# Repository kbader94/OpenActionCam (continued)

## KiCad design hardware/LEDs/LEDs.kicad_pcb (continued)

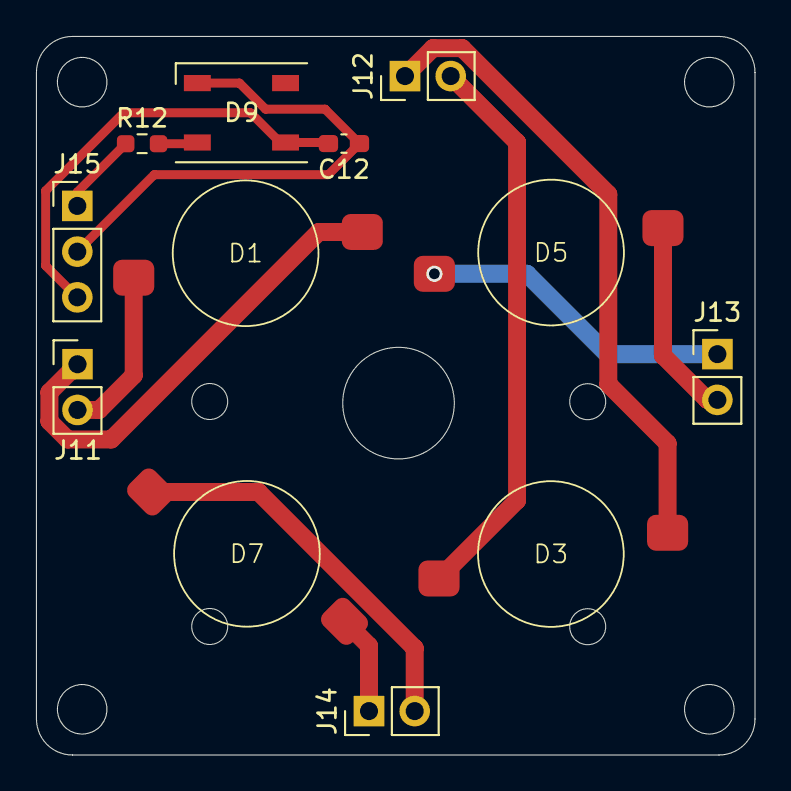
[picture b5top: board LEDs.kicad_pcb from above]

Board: 2 copper layers, 39.9 x 39.9 mm, 12 parts (0 on the bottom side), 11 nets.

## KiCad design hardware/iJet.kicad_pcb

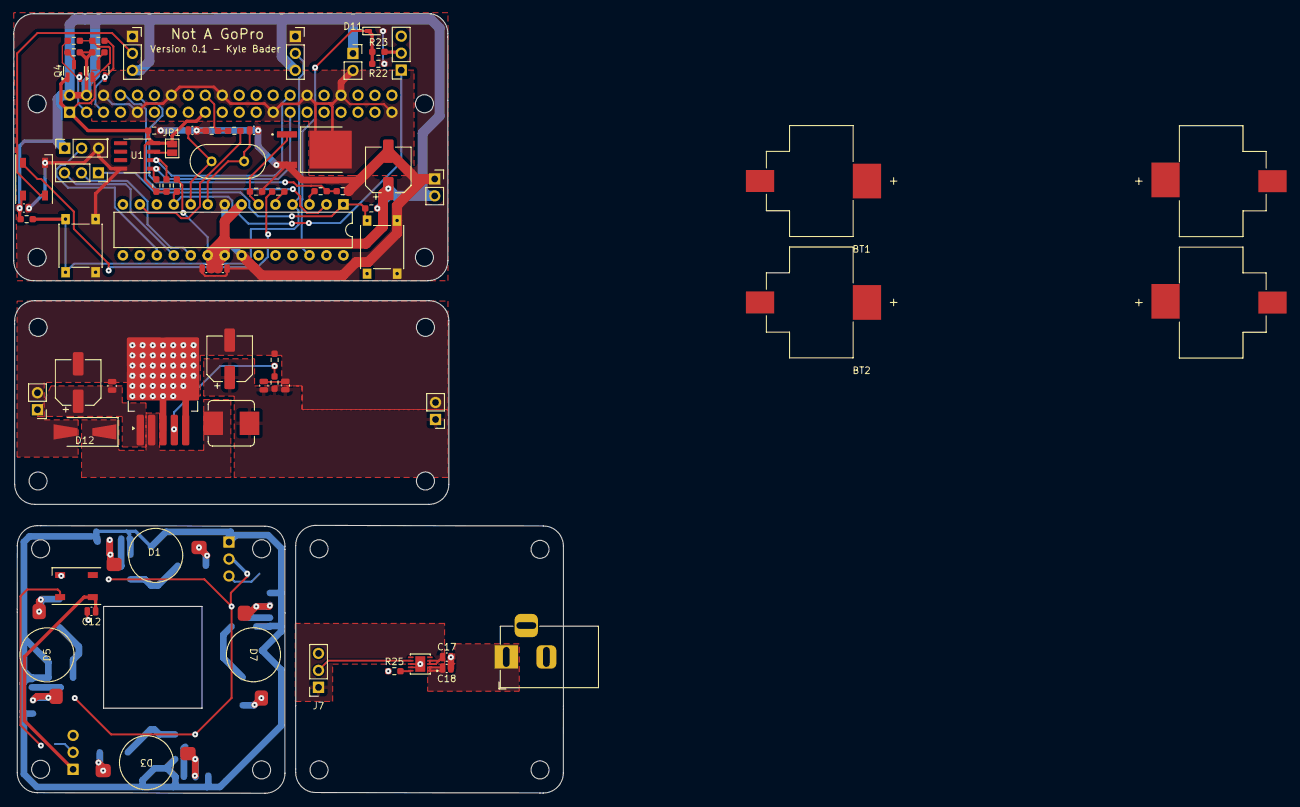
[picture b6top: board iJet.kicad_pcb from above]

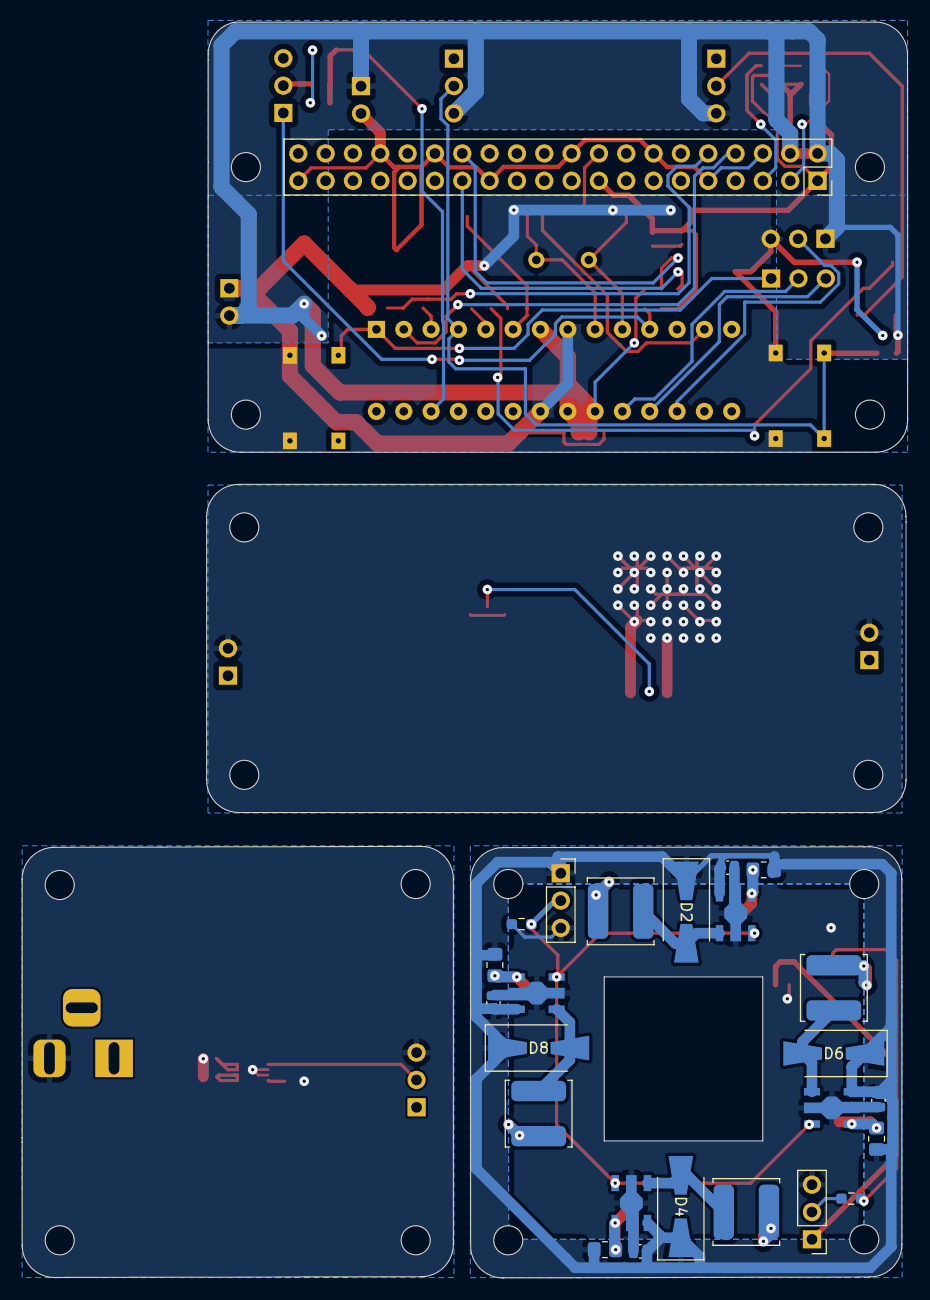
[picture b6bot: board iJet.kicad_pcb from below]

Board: 2 copper layers, 82.3 x 116.7 mm, 109 parts (25 on the bottom side), 48 nets.

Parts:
BT1, BT2: Battery_Cell; BAT_254
C1: 100n; R_0603_1608Metric_Pad0.98x0.95mm_HandSolder
C2: 100 UF; C_0504_1310Metric_Pad0.83x1.28mm_HandSolder
C3, C4, C5: 100 uF; C_0504_1310Metric_Pad0.83x1.28mm_HandSolder
C6, C12, C19: 0.1uF; C_0504_1310Metric_Pad0.83x1.28mm_HandSolder
C7: C_Polarized; CP_Elec_6.3x5.9
C8: 100uF 25V; CP_Elec_6.3x5.9
C9: 330uF 10V; CP_Elec_6.3x5.9
C10: 10nF; C_0504_1310Metric_Pad0.83x1.28mm_HandSolder
C11: 0.1uF 25V; C_0504_1310Metric_Pad0.83x1.28mm_HandSolder
C13, C14: 100nF; C_0504_1310Metric_Pad0.83x1.28mm_HandSolder
C15, C16: 22 pF; C_0504_1310Metric_Pad0.83x1.28mm_HandSolder
C17, C18: 10uF XR5/7; C_0504_1310Metric_Pad0.83x1.28mm_HandSolder
D1, D3: 3W LED; BEAD-3W-W-120-04
D2, D4, D6, D8: SS14; D_SMA-SMB_Universal_Handsoldering
D5, D7: LED; BEAD-3W-W-120-04
D9, D10: WS2812B; LED_WS2812B_PLCC4_5.0x5.0mm_P3.2mm
D11: 5.1V Zener; D_SC-80_HandSoldering
D12: 1N5825; D_SMA-SMB_Universal_Handsoldering
J1: GPIO; PinSocket_2x20_P2.54mm_Vertical
J2: Status_LED_Header; PinHeader_1x03_P2.54mm_Vertical
J3: HP_LED_Header; PinSocket_1x03_P2.54mm_Vertical
J4: Barrel_Jack; BarrelJack_Horizontal
J5: Battery_In; PinHeader_1x02_P2.54mm_Vertical
J6: 5V Out; PinHeader_1x02_P2.54mm_Vertical
J7: Conn_01x03_Socket; PinSocket_1x03_P2.54mm_Vertical
J12: Battery_Meas; PinSocket_1x03_P2.54mm_Vertical
J13: ICSP_Header_2; PinSocket_1x03_P2.54mm_Vertical
J14: 5V_In; PinSocket_1x02_P2.54mm_Vertical
J15: Stat_LED; PinSocket_1x03_P2.54mm_Vertical
J16: ICSP_Header_1; PinSocket_1x03_P2.54mm_Vertical
J17: Button_Header; PinSocket_1x03_P2.54mm_Vertical
J18: RPI_POWER; PinSocket_1x02_P2.54mm_Vertical
JP1: ID_WP; SolderJumper-2_P1.3mm_Open_Pad1.0x1.5mm
L1, L2, L3, L4: 68 uH; L_TDK_VLS6045EX_VLS6045AF
L5: 33uH; L_Bourns_SRP7028A_7.3x6.6mm
MH1, MH1#2, MH1#3, MH2, MH2#2, MH2#3, MH3, MH3#2, MH3#3, MH4, MH4#2, MH4#3, MH4#4, MH4#5, MH4#6, MH4#7: MountingHole_2.7mm_M2.5
Q2: AOD4184A; DPAK228P994X240-4N
Q3, Q4: BSS138; SOT-23
R1, R2: 3.9k; R_0603_1608Metric_Pad0.98x0.95mm_HandSolder
R3: 0.15 Ohm; R_0805_2012Metric_Pad1.20x1.40mm_HandSolder
R4, R5, R6: 0.15; R_0805_2012Metric_Pad1.20x1.40mm_HandSolder
R7, R11, R13, R14, R15, R16, R21, R23, R24: 10K; R_0603_1608Metric_Pad0.98x0.95mm_HandSolder
R8: 220 Ohm (Opt); R_0603_1608Metric_Pad0.98x0.95mm_HandSolder
R9: 3.065 K; R_0603_1608Metric_Pad0.98x0.95mm_HandSolder
R10, R25: 1K; R_0603_1608Metric_Pad0.98x0.95mm_HandSolder
R12, R26: R; R_0603_1608Metric_Pad0.98x0.95mm_HandSolder
R17, R20: 3.3K; R_0603_1608Metric_Pad0.98x0.95mm_HandSolder
R18, R19: 2K; R_0603_1608Metric_Pad0.98x0.95mm_HandSolder
R22: 15K; R_0603_1608Metric_Pad0.98x0.95mm_HandSolder
SW1: SW_DIP_x01; Button_Sw_THT
SW2: SW_Reset; Button_Sw_THT
U1: CAT24C256; SOIC127P600X175-8N
U2: LM2596S-ADJ; TO-263-5_TabPin3
U4: ATmega328-P; DIP-28_W7.62mm
U5, U6, U7, U8: PT4115; SOT-89-5
U9: MCP73213-A6SI_MF; SON50P300X300X100-11N
Y2: 16 Mhz; Crystal_HC49-U_Vertical

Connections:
+3V3: C1.1, J1.1, J1.17, JP1.2 (B), Q3.1 (G), Q4.1 (G), R1.1, R2.1, R13.2, R16.2, U1.8 (VCC)
+5V: C6.2, C7.1, C9.1, C10.2, C12.2, C13.2, C14.2, C19.1, D9.1 (VDD), D10.1 (VDD), J1.2, J1.4, J2.1, J6.1, J14.2, J15.3, J16.1, J17.3, J18.1, L5.2, R9.1, R14.2, R15.2, R21.1, R24.1, R26.1, U4.7 (VCC), U4.20 (AVCC), U4.21 (AREF)
+BATT: C2.1, C3.1, C4.1, C5.1, C8.1, C11.1, C17.1, D2.1 (K), D4.1 (K), D6.1 (K), D8.1 (K), J3.1, J5.1, J7.1, R3.1, R4.1, R5.1, R6.1, U2.1 (VIN), U5.5 (VIN), U6.5 (VIN), U7.5 (VIN), U8.5 (VIN), U9.3 (VBAT), U9.4 (VBAT)
/GPIO2/SDA1: J1.3, Q4.2 (S), R16.1
/GPIO3/SCL1: J1.5, Q3.2 (S), R13.1
/GPIO14/TXD0: J1.8, U4.2 (PD0)
/GPIO15/RXD0: J1.10, R17.2, R18.1
/GPIO24: J1.18, R19.1, R20.2
/ID_SCL: J1.28, R2.2, U1.6 (SCL)
/ID_SDA: J1.27, R1.2, U1.5 (SDA)
/LED Array/LED_En: J3.2, R11.1, U5.3 (DIM), U6.3 (DIM), U7.3 (DIM), U8.3 (DIM)
/LED Array/Status_DIN: J2.2, R8.1, R12.1, U4.5 (PD3)
/Pi_Int: R20.1, U4.13 (PD7)
/Pi_Rx: R17.1, U4.3 (PD1)
/Power Port and Charger/12V_IN: C18.1, J4.1, U9.1 (VDD), U9.2 (VDD)
/Power Port and Charger/Chrg_Stat: J7.2, J12.1, R26.2, U4.11 (PD5), U9.7 (STAT)
/Power State/BDI: J17.2, R24.2, SW1.1, U4.4 (PD2)
/Power State/Batt_Lvl: D11.1 (K), J12.2, R22.2, R23.1, R23.2, U4.26 (PC3)
/Power State/MISO: J13.3, U4.18 (PB4)
/Power State/MOSI: J16.2, U4.17 (PB3)
/Power State/Pi_En: Q2.1, R7.1, U4.6 (PD4)
/Power State/Reset: J13.1, R21.2, SW2.1, U4.1 (~RESET/PC6)
/Power State/SCK: J13.2, U4.19 (PB5)
/Power Supply/V_Out_Dirty: D12.1 (K), L5.1, U2.2 (OUT)
/SCL: Q3.3 (D), R14.1
/SDA: Q4.3 (D), R15.1
GND: C1.2, C2.2, C3.2, C4.2, C5.2, C6.1, C7.2, C8.2, C9.2, C10.1, C11.2, C12.1, C13.1, C14.1, C15.2, C16.2, C17.2, C18.2, C19.2, D9.3 (VSS), D10.3 (VSS), D11.2 (A), D12.2 (A), J2.3, J3.3, J4.2, J5.2, J6.2, J7.3, J14.1, J15.1, J16.3, J17.1, Q2.3, R7.2, R10.1, R11.2, R18.2, R19.2, R22.1, R25.1, SW1.2, SW2.2, U1.4 (GND), U2.3 (GND), U2.5 (~ON/OFF), U4.8 (GND), U4.22 (GND), U5.2 (GND), U6.2 (GND), U7.2 (GND), U8.2 (GND), U9.8 (VSS), U9.9 (VSS), U9.11 (EP)
unnamed: D1.2 (A), R3.2, U5.4 (CSN)
unnamed: D1.1 (K), L1.1
unnamed: D2.2 (A), L1.2, U5.1 (SW)
unnamed: D3.2 (A), R4.2, U6.4 (CSN)
unnamed: D3.1 (K), L2.1
unnamed: D4.2 (A), L2.2, U6.1 (SW)
unnamed: D5.2 (A), R5.2, U7.4 (CSN)
unnamed: D5.1 (K), L3.1
unnamed: D6.2 (A), L3.2, U7.1 (SW)
unnamed: D7.2 (A), R6.2, U8.4 (CSN)
unnamed: D7.1 (K), L4.1
unnamed: D8.2 (A), L4.2, U8.1 (SW)
unnamed: D9.4 (DIN), R12.2
unnamed: D10.4 (DIN), R8.2
unnamed: D10.2 (DOUT), J15.2
unnamed: JP1.1 (A), U1.7 (WP)
unnamed: R9.2, R10.2, U2.4 (FB)
unnamed: C15.1, U4.9 (XTAL1/PB6), Y2.2
unnamed: C16.1, U4.10 (XTAL2/PB7), Y2.1
unnamed: R25.2, U9.10 (PROG)
Pi_Gnd: J1.6, J1.9, J1.14, J1.20, J1.25, J1.30, J1.34, J1.39, J18.2, Q2.4

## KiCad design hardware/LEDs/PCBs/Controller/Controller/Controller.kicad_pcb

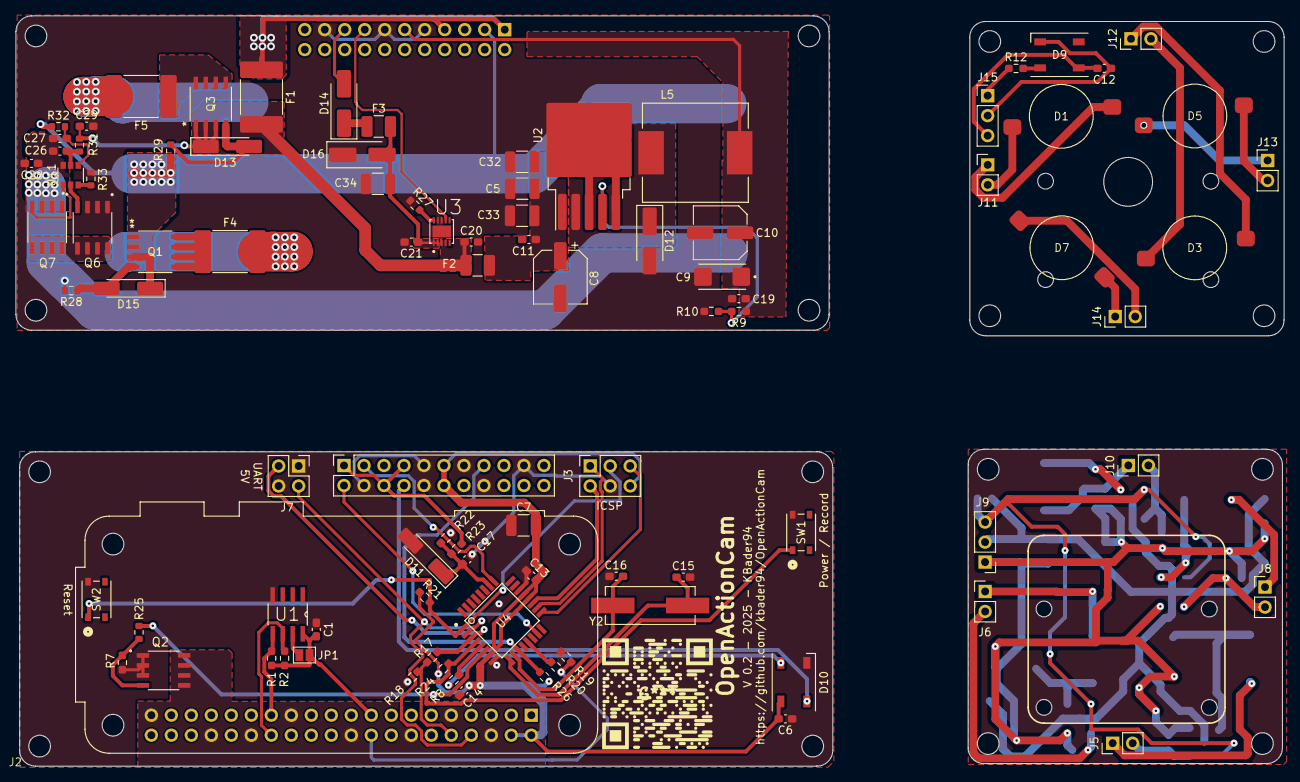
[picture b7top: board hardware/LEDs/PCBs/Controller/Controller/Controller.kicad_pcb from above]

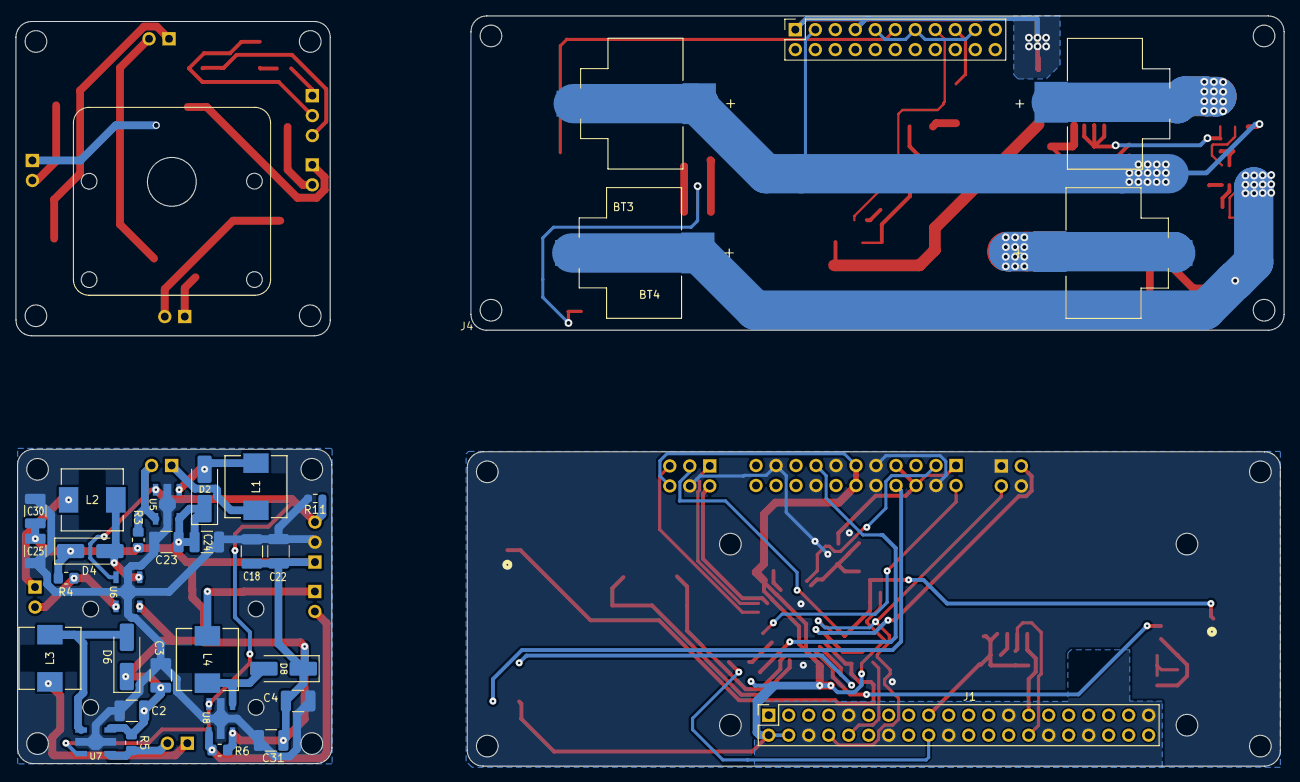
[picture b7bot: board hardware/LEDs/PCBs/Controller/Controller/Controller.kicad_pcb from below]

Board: 2 copper layers, 161.1 x 95.3 mm, 123 parts (31 on the bottom side), 71 nets.

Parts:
BT3, BT4: Battery_Cell; BAT_254
C1: 100n; C_0603_1608Metric_Pad1.08x0.95mm_HandSolder
C2, C3, C4, C5, C18, C22, C23, C24, C25, C30, C31: 47uF 1210; R_1210_3225Metric_Pad1.30x2.65mm_HandSolder
C6, C12, C26, C29: 0.1uF; C_0603_1608Metric_Pad1.08x0.95mm_HandSolder
C7: 47uF 1210; C_1210_3225Metric_Pad1.33x2.70mm_HandSolder
C8: 100uF 16V; CP_Elec_6.3x7.7
C9: 330uF Tant 2312; CAPPM6032X280N
C10: 330uF 10V Elec; C_Elec_6.3x7.7
C11: 0.1uF 25V; C_0603_1608Metric_Pad1.08x0.95mm_HandSolder
C13, C14, C17: 100nF; C_0603_1608Metric_Pad1.08x0.95mm_HandSolder
C15, C16: 22 pF; C_0603_1608Metric_Pad1.08x0.95mm_HandSolder
C19: 0.1uF 0603; C_0603_1608Metric_Pad1.08x0.95mm_HandSolder
C20, C21: 10uF 0805; C_0603_1608Metric_Pad1.08x0.95mm_HandSolder
C27: 0.1 uF; C_0603_1608Metric_Pad1.08x0.95mm_HandSolder
C28: 0.1uF OPT; C_0603_1608Metric_Pad1.08x0.95mm_HandSolder
C32, C33: 47uF; R_1210_3225Metric_Pad1.30x2.65mm_HandSolder
C34: 47uF - 1210; R_1210_3225Metric_Pad1.30x2.65mm_HandSolder
D1, D3, D5, D7: 3W LED; BEAD-3W-W-120-04
D2, D4, D6, D8: SS14; D_SMA_Handsoldering
D9, D10: WS2812B; LED_WS2812B_PLCC4_5.0x5.0mm_P3.2mm
D11: 5.1V Zener; D_MiniMELF_Handsoldering
D12: SS34; D_SMA_Handsoldering
D13, D15: 9.1V Zener; D_MiniMELF_Handsoldering
D14: SS24; D_SMA_Handsoldering
D16: SMAJ11A; D_SMA_Handsoldering
F1: 6A Polyfuse 2920; Fuse_2920_7451Metric_Pad2.10x5.45mm_HandSolder
F2: 2.2A Polyfuse 1210; Fuse_1210_3225Metric_Pad1.42x2.65mm_HandSolder
F3: 2.2A Polyfuse; Fuse_1210_3225Metric_Pad1.42x2.65mm_HandSolder
F4, F5: Polyfuse 6A 2920; Fuse_2920_7451Metric_Pad2.10x5.45mm_HandSolder
J1: GPIO; Raspberry_Pi_Zero_Socketed_THT_FaceDown_MountingHoles
J2: Conn_02x11_Counter_Clockwise; Board_outline
J3: ICSP Header; PinSocket_2x03_P2.54mm_Vertical
J4: Conn_01x11; Board_outline
J5, J8, J9, J10, J11, J12, J13, J14: Conn_01x02_Pin; PinHeader_1x02_P2.54mm_Vertical
J6: Conn_01x03; PinHeader_1x03_P2.54mm_Vertical
J7: UART DEBUG; PinSocket_2x02_P2.54mm_Vertical
J15: LED_Board_Header; PinHeader_1x03_P2.54mm_Vertical
JP1: ID_WP; SolderJumper-2_P1.3mm_Open_Pad1.0x1.5mm
L1, L2, L3, L4: 68 uH; DR74
L5: 33uH; IND_125CDMCCDS-330MC
Q1, Q3: PMOS; SO-8_VIS
Q2: NMOS; SOIC127P490X600X175-8N
Q6, Q7: AOSP36326C; SOIC127P490X600X175-8N
R1, R2: 3.9k; R_0603_1608Metric_Pad0.98x0.95mm_HandSolder
R3: 0.15 - 0805; R_0805_2012Metric_Pad1.20x1.40mm_HandSolder
R4: 0.15 -0805; R_0805_2012Metric_Pad1.20x1.40mm_HandSolder
R5, R6: 0.15; R_0805_2012Metric_Pad1.20x1.40mm_HandSolder
R7, R11, R21, R23, R24: 10K; R_0603_1608Metric_Pad0.98x0.95mm_HandSolder
R8: 220; R_0603_1608Metric_Pad0.98x0.95mm_HandSolder
R9: 3.1K 0603; R_0603_1608Metric_Pad0.98x0.95mm_HandSolder
R10: 1K 0603; R_0603_1608Metric_Pad0.98x0.95mm_HandSolder
R12: 0; R_0603_1608Metric_Pad0.98x0.95mm_HandSolder
R17, R20: 3.3K; R_0603_1608Metric_Pad0.98x0.95mm_HandSolder
R18, R19: 2K; R_0603_1608Metric_Pad0.98x0.95mm_HandSolder
R22: 15K; R_0603_1608Metric_Pad0.98x0.95mm_HandSolder
R25, R26: 10K; R_0603_1608Metric
R27: 1K 0603; R_0603_1608Metric
R28, R29: 100K; R_0603_1608Metric
R31, R32: 330; R_0603_1608Metric
R33: 2.2K; R_0603_1608Metric
SW1: Button - User Interface; SW4_PTS815 SJM 250 SMTR LFS_CNK
SW2: Button - Reset; SW4_PTS815 SJM 250 SMTR LFS_CNK
U1: CAT24C256; SOIC127P600X175-8N
U2: LM2596S-ADJ; TO-263-5_TabPin3
U3: MCP73213-A6SI_MF; SON50P300X300X100-11N
U4: ATmega328-P; QFP80P900X900X120-32N
U5, U6, U7, U8: PT4115; SOT-89-5
U11: MM3220AA2NRH; IC_MM3220AA2NRH
Y2: 16 Mhz; XTAL_ECS-160-20-5PX-TR

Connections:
8.4V: C2.1, C3.1, C4.1, C18.1, C20.1, C22.1, C23.1, C24.1, C25.1, C29.1, C30.1, C31.1, D2.1 (K), D4.1 (K), D6.1 (K), D8.1 (K), D13.1 (K), F1.2, F2.1, J2.1, J2.4, J2.14, J6.1, Q3.3 (S), R3.1, R4.1, R5.1, R6.1, R23.2, R31.2, U3.3 (VBAT), U3.4 (VBAT), U5.5 (VIN), U6.5 (VIN), U7.5 (VIN), U8.5 (VIN)
+3V3: C1.1, J1.1, J1.17, JP1.2 (B), R1.1, R2.1, U1.8 (VCC)
+5V: C6.2, C7.2, C9.1, C10.1, C12.2, C13.2, C14.2, C19.1, D9.1 (VDD), D10.1 (VDD), J1.2, J1.4, J2.6, J2.17, J3.6, J4.6, J15.3, L5.2, R9.1, R21.1, R24.1, R26.1, U4.7 (VCC), U4.20 (AVCC), U4.21 (AREF)
+12V: C21.1, C34.2, D16.2 (A2), F3.2, U3.1 (VDD), U3.2 (VDD)
/GPIO15/RXD0: J1.10, R17.2, R18.1
/GPIO24: J1.18, R19.1, R20.2
/ID_SCL: J1.28, R2.2, U1.6 (SCL)
/ID_SDA: J1.27, R1.2, U1.5 (SDA)
/Power BMS/8.4V Out: F1.1, J4.1, J4.4
/Power BMS/Battery Pack & Protection/8.4unsafe: F5.1, Q3.1 (D)
/Power BMS/Battery Pack & Protection/d2d: Q6.1 (D), Q7.1 (D)
/Power BMS/Power Supply/V_Out_Dirty: D12.1 (K), L5.1, U2.2 (OUT)
/Power BMS/Power Supply/Vin_clean: C5.1, C8.1, C11.1, C32.1, C33.1, F2.2, U2.1 (VIN)
/Power State/Batt_Lvl: C17.2, D11.1 (K), R22.2, R23.1, U4.26 (PC3)
/Power State/MISO: J3.1, U4.18 (PB4)
/Power State/MOSI: J3.5, U4.17 (PB3)
/Power State/Pi_En: R25.1, U4.6 (PD4)
/Power State/Reset: J3.3, R21.2, SW2.1, U4.1 (~RESET/PC6)
/Power State/SCK: J3.2, U4.19 (PB5)
/Power State/STAT_LED_OB: R8.1, U4.5 (PD3)
BATT_LVL-: BT4.2 (-), C26.1, C27.2, C28.2, Q7.3 (S), R28.2, U11.6 (VSS)
BATT_LVL_MID: BT3.2 (-), D15.1 (K), J2.2, J4.2, Q1.3 (S), R29.2, R32.1, U4.25 (PC2)
Button: J2.18, R24.2, SW1.1, U4.4 (PD2)
Chrg_Stat: J2.8, J4.8, R26.2, U3.7 (STAT), U4.11 (PD5)
GND: C1.2, C2.2, C3.2, C4.2, C5.2, C6.1, C7.1, C8.2, C9.2, C10.2, C11.2, C12.1, C13.1, C14.1, C15.2, C16.2, C17.1, C18.2, C19.2, C20.2, C21.2, C22.2, C23.2, C24.2, C25.2, C28.1, C29.2, C30.2, C31.2, C32.2, C33.2, C34.1, D9.3 (VSS), D10.3 (VSS), D11.2 (A), D12.2 (A), D16.1 (A1), J2.5, J2.7, J2.10, J2.13, J2.16, J2.19, J3.4, J4.5, J4.7, J4.10, J6.2, J7.1, J7.4, J15.2, Q2.3 (S), Q6.3 (S), R7.2, R10.1, R11.2, R18.2, R19.2, R22.1, R27.1, R33.2, SW1.2, SW2.2, U1.4 (GND), U2.3 (GND), U2.5 (~ON/OFF), U3.8 (VSS), U3.9 (VSS), U3.11 (EP), U4.8 (GND), U4.22 (GND), U5.2 (GND), U6.2 (GND), U7.2 (GND), U8.2 (GND)
LED_EN: J2.12, J6.3, R11.1, U4.15 (PB1), U5.3 (DIM), U6.3 (DIM), U7.3 (DIM), U8.3 (DIM)
unnamed: BT3.1 (+), F5.2
unnamed: BT4.1 (+), F4.2
unnamed: D1.2 (A), J11.2
unnamed: D1.1 (K), J11.1
unnamed: D2.2 (A), L1.2, U5.1 (SW)
unnamed: D3.2 (A), J12.2
unnamed: D3.1 (K), J12.1
unnamed: D4.2 (A), L2.2, U6.1 (SW)
unnamed: D5.2 (A), J13.2
unnamed: D5.1 (K), J13.1
unnamed: D6.2 (A), L3.2, U7.1 (SW)
unnamed: D7.2 (A), J14.2
unnamed: D7.1 (K), J14.1
unnamed: D8.2 (A), L4.2, U8.1 (SW)
unnamed: D9.4 (DIN), R12.2
unnamed: D10.4 (DIN), R8.2
unnamed: D13.2 (A), Q3.2 (G), R29.1
unnamed: D14.2 (A), J4.9
unnamed: D14.1 (K), F3.1
unnamed: D15.2 (A), Q1.2 (G), R28.1
unnamed: J5.1, L3.1
unnamed: J5.2, R5.2, U7.4 (CSN)
unnamed: J8.1, L2.1
unnamed: J8.2, R4.2, U6.4 (CSN)
unnamed: J9.1, L4.1
unnamed: J9.2, R6.2, U8.4 (CSN)
unnamed: J10.1, L1.1
unnamed: J10.2, R3.2, U5.4 (CSN)
unnamed: JP1.1 (A), U1.7 (WP)
unnamed: F4.1, Q1.1 (D)
unnamed: Q2.2 (G), R7.1, R25.2
unnamed: Q6.2 (G), U11.2 (COUT)
unnamed: Q7.2 (G), U11.1 (DOUT)
unnamed: R9.2, R10.2, U2.4 (FB)
unnamed: R27.2, U3.10 (PROG)
unnamed: C15.1, U4.9 (XTAL1/PB6), Y2.2
unnamed: C16.1, U4.10 (XTAL2/PB7), Y2.1
unnamed: R33.1, U11.3 (V-)
unnamed: C27.1, R32.2, U11.4 (VBL)
unnamed: C26.2, R31.1, U11.5 (VDD)
Pi_Gnd: J1.6, J1.9, J1.14, J1.20, J1.25, J1.30, J1.34, J1.39, Q2.1 (D)
Pi_Int: R20.1, U4.13 (PD7)
Rx: J1.8, J7.3, U4.2 (PD0)
STAT_LED: D10.2 (DOUT), J2.15, J15.1, R12.1
Tx: J7.2, R17.1, U4.3 (PD1)

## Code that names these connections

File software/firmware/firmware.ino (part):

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#include "rainbow_led_animation.h"
#include "system_state.h"

#define BUTTON_PIN 2   /* Button on PD2 (INT0), atmega328 physical pin 4, AKA arduino digital 2 */
#define STAT_LED_PIN 3 /* WS2812 LED strip on PD3, atmega328 physical pin 5, AKA arduino digial 3 */
#define POWER_PIN 4    /* MOSFET control on PD4, atmega328 physical pin 6, AKA arduino digital 4 */
#define CHRG_STAT 5    /* Charger status on PD5, atmega physical pin 9, AKA arduino digital 5*/
#define PI_INT 7       /* RPI Interrupt on PD7, atmega328 physical pin 13, AKA arduino digital 7 */
#define LED_EN 9       /* Enable LED on PB1, atmega physical pin 15, AKA arduino digital 9 */

#define DEBOUNCE_DELAY 50       /* Button debounce delay (ms) */
#define LONG_PRESS_TIME 1000    /* Long press threshold (ms) */
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


Adafruit_NeoPixel led_strip(1, STAT_LED_PIN, NEO_GRB + NEO_KHZ800);
Led led(&led_strip, 0);
SystemStateManager system_state(&led, POWER_PIN);

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
    /* Get ADC samples */
    for (uint8_t i = 0; i < BATTERY_SAMPLES; i++) {
        ADMUX = (1 << REFS0) | (1 << MUX1) | (1 << MUX0); /* PC3 / A3 */ 
        ADCSRA |= (1 << ADSC);
        while (ADCSRA & (1 << ADSC));
        sum += ADC;
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    /* init pins */
    pinMode(BUTTON_PIN, INPUT_PULLUP);
    pinMode(POWER_PIN, OUTPUT);
    pinMode(CHRG_STAT, INPUT_PULLUP);

    /* button interrupt */
    attachInterrupt(digitalPinToInterrupt(BUTTON_PIN), button_isr, CHANGE);

    /* charger status interrupt*/
    PCICR |= (1 << PCIE2);      /* Enable PCINT[23:16] */
    PCMSK2 |= (1 << PCINT21);   /* Enable interrupt on PD5 (digital 5 / PCINT21) */
    charging = digitalRead(CHRG_STAT) == LOW;


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
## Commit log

2025-02-27 Initial commit
    Initial implementation of basic power state management and IO prototype
    V0.1
    Changes to be committed:
    new file: blink_led_animation.cpp
    new file: blink_led_animation.h
    new file: error.cpp
2025-03-01 Modifies throwError and blink_led_animation to be singleton's with updatable error code to allow resetting device with errors from the UI button. Adds initial file to seperate logic for Power Mangeme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
    On branch master
    Changes to be committed:
    modified: blink_led_animation.cpp
    modified: blink_led_animation.h
    modified: error.cpp
    modified: error.h
2025-03-02 Modifies error handling to use Macros, supports warnings and debug messaging. Also integrates the logic for device state changes during errors into the error handler itself for better SoC.
    On branch master
    Changes to be committed:
    modified: error.cpp
    modified: error.h
    modified: iJet.ino
    modified: power_management.cpp
2025-03-17 Refactor entire project - move arduino code to /arduino Import rpi code in /linux Create comms.c - portable serial comms between atmega and linux Add symlinks to comms.c and comms.h in /arduino and /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
2025-03-18 Major Project Refactor Finished implementing comms.c - portable comms code Create serial_wrapper to facilitage portable comms code Rename arduino directory to firmware Add makeFile for linux program 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
2025-03-18 cross compile linux program
2025-03-20 implement error handling on linux system
2025-03-20 Send errors to firmware cleanup comms.h
2025-03-21 Implements error forwarding on firmware. Errors on the linux system can now be forwarded to the firmware to display to the user. Refactor power_management to use comms.c for commands Initialize messa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
2025-03-21 various syntactic and semantic fixes
2025-03-23 firmware - formatting & cleanup linux/error.h comms_send_error() linux/main.c listen for Error Messages linux/record.c - Monitor recording output for errors comms.c/h - serialize & deserialize messge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
2025-03-24 Add debug support for linux_camera in scripts and makefile firmware cleanup comms cleanup and error handling
2025-03-25 Error Handling refactor error.h/cpp - * Make code portable and shared between linux and firmware. * Change error definitions to include device origin. Do not send errors back to origin. * Properly in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
2025-03-25 Error Handling Cleanup * Slow down LED blink in firmware * Fix/add throw_error() in linux/error.cpp * Reduce error code ints for better readability via LED
2025-03-26 import hardware
2025-03-26 cleanup hardware
2025-03-27 Firmware - Support low power sleep * Add support for sleep via power-down and wake on interrupt INT0 * Fixed broken script paths after importing hardware and moving software
2025-03-29 Disable peripherals in low power state * Add logic to disable and re-enable peripherals when entering and exiting a low power state
2025-03-29 Transmit status
    firmware.ino:
    * implements read_battery_voltage() - read battery level
    * implements transmit_status_message - Periodically transmit a status message
    * code cleanup: rename press_duration to button_press_duration for clarity
    comms.h:
    * refactor struct StatusBody to use float for battery_level and uint8 for error_code
2025-03-30 Process status messages
    linux software
    * Refactor main loop to process status messsages
    * code cleanup in main.c: use DEBUG_MESSAGE macro instead of printf
    firmware:
    * firmware.ino - sleep_until_button_press is broken, disable for now.
2025-03-31 Firmware errors for low and high battery voltages firmware.ino: * change read_battery_voltage() to average multiple samples * add check for battery voltage level errors in main loop
    error.h:
    * Add low and high battery voltage error definition macros, ERR_LOW_BATTERY and ERR_BATTERY_OV
2025-04-06 Hardware V0.2 - Schematics update
    Combines Cell holder, BMS, and voltage regulator into single board
    complete w. extensive electrical and thermal protections including:
    * MM3220 BMS w Overvoltage, Overcurrent, undervoltage charging/discharge protect
    * Fuses on cells, 12v in, 5v and 8.4v out.
    * Reverse polarity protection on 12v and cells.
    Adds debug UART header
2025-04-11 Hardware revision 0.2 routing
2025-04-12 Seperate PCBs into individual KiCAD projects
2025-04-18 Hardware cleanup & enclosure prototype
    * Seperates the kicad project into seperate projects per PCB
    * initial FreeCAD Assets and prototypes added
2025-05-10 Hardware - Controller - Rev 0.3
    * Consolidate various asset dirs into single symlinked directory.
    * Fixes major flaw with previous atmega328 layout - wrong schematic symbol caused incorrect routing
    * Use smaller crystal closer to mcu
    * Add QR to silkscreen
2025-05-11 Update comms protocol
    * Move checksum into header;
    * Checksum entire message incl header;
    Initial Watchdog driver
    * Export oac_send_message from oac_dev.c;
    * Add watchdog ops to oac_watchdog.c;
2025-05-13 OAC driver * Fix compile error in oac_watchdog.c * Fix: return actual error val(-EINVAL) in oac_send_message
2025-05-15 Watchdog Driver & OACD watchdog service
    OAC Drivers
    * Implement watchdog driver, inc start,stop, and ping wdd->ops
    * Rename oac directory and install script to drivers
    OACD
    * Implement oacd - systemd service for oacd watchdog services. Pings systemd AND watchdog device(/dev/watchdog1)
    * Implement oacd makefile and remote install script
2025-05-17 Support for oac watchdog driver from firmware side
    oac_dev.c - Core serdev driver
    * Fix - use proper serial baud rate
    oac_comms.c - serdev comms
    * Fix - validate checksum
    * Fix - move checksum into header during serialization
    comms.c - firmware comms
2025-05-17 clarify and cleanup comms.c
2025-05-21 oac_comms.c & comms.c * Refactor - change get_param / set_param to command / response
    oac_dev.c
    * Implement oac_dev_register_callback
    * Implement oac_dev_unregister_callback
    * Implement oac_dev_message_registered_callbacks
    oac_button.c
    * Initial implementation of button input dev driver
2025-05-25 REFACTOR power_management => system_state * Refactor power_management * Implement function for processStateTransition to seperate logic for state transition
2025-05-25 oac_battery.c
    * Fix(dur) - change Message struct StatusBody to use uint32
    * Implement oac_battery.c - battery driver
2025-05-26 fix - LED on when dev off
2025-05-29 ALL THE FIXES
    This commit contains all the fixes for initial implementations of oac_watchdog, oac_button, and oac_battery. At this point the
    firmware.ino
    * Fix battery voltage always low
    oac_battery.c
    * Make *bat global singleton
    * use psy_cfg in oac_batty_probe
2025-05-31 oac_battery.c - battery level patch
    * implements several new POWER_SUPPLY_PROPs which enable upower to detect battery capacity
    * add bat_lvl to StatusBody. bat_lvl is a firmware calculated percentage between 0 and 100 reprepresenting approximate charge level.
2025-06-01 oac_battery
    * implement shutdown upon critically low battery level.
2025-06-01 modified: software/linux/drivers/oac_battery.c
